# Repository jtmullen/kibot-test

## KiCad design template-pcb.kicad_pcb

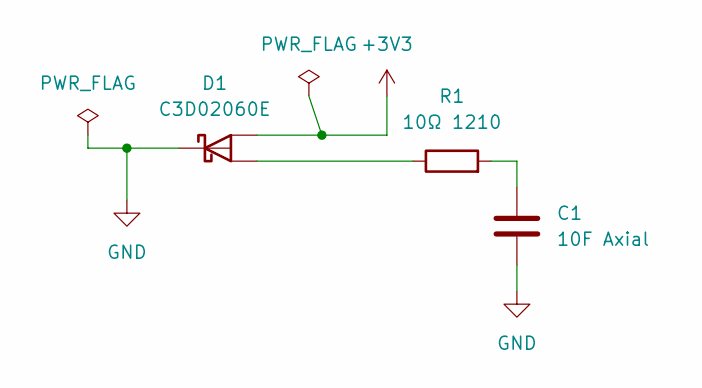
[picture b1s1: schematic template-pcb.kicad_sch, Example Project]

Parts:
C1: 10F Axial; CP_Axial_L10.0mm_D4.5mm_P15.00mm_Horizontal
D1: C3D02060E; TO-277A; MPN CTLSH4-200M364
R1: 10Ω 1210; R_1210_3225Metric_Pad1.30x2.65mm_HandSolder

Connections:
+3V3: D1.2 (A)
GND: C1.2, D1.3 (K)
unnamed: C1.1, R1.2
unnamed: D1.1 (A), R1.1

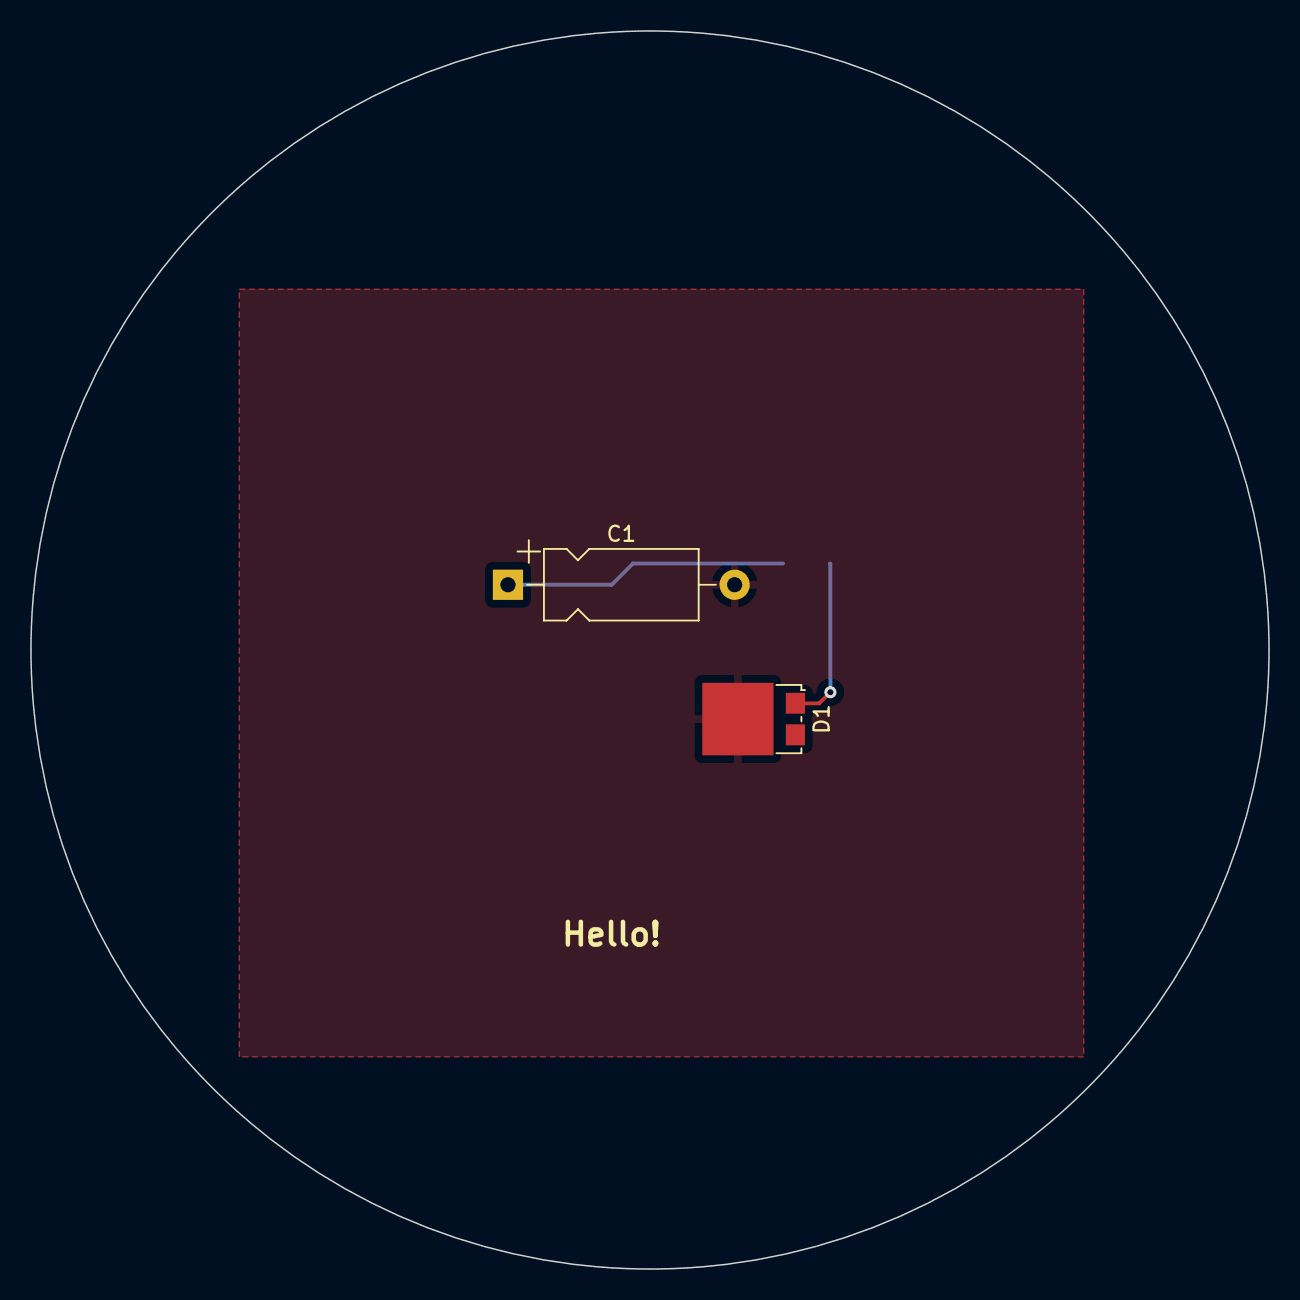
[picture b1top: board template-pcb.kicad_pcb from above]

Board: 2 copper layers, 81.9 x 81.9 mm, 3 parts (1 on the bottom side), 3 nets.

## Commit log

2023-03-30 Example run
2023-03-30 Permissions
2023-03-31 dev container
2023-03-31 full path
